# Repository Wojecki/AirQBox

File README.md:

# AirQBox
Simple air quality measuring box. 

<hr>
The project uses a custom PCB ordered from JLCPCB. It isn't required to build the box, but it makes wiring much easier and gives the whole setup a much cleaner look. The PCB is also prepared for additional components, such as a button or another I2C sensor, and does not have to be fully populated as shown in the photos above.
<hr>

<hr>
A potential use case is a home IoT weather station using web interface and OpenWeather API.
<hr>

<hr>
Bill of Materials (BOM)

| Category | Component | Description / Model | Interface |
| :--- | :--- | :--- | :--- |
| **Microcontroller** | ESP32 Dev Board | 30-pin version (15 pins per side) | — |
| **Display** | E-Ink Display Module | 4.2" 400×300 px e-Paper (Waveshare 13353) | SPI |
| **Sensor** | AHT20 + BMP280 | Temperature, humidity, and barometric pressure sensor module | I2C |
| **Sensor** | SGP30 | Indoor air quality sensor (TVOC & eCO₂) | I2C |
| **Sensor** | SCD40 | True NDIR CO₂ sensor (with temp & humidity) | I2C |
| **Sensor** | PMS5003 | Laser particulate matter sensor (PM1.0, PM2.5, PM10) | UART |

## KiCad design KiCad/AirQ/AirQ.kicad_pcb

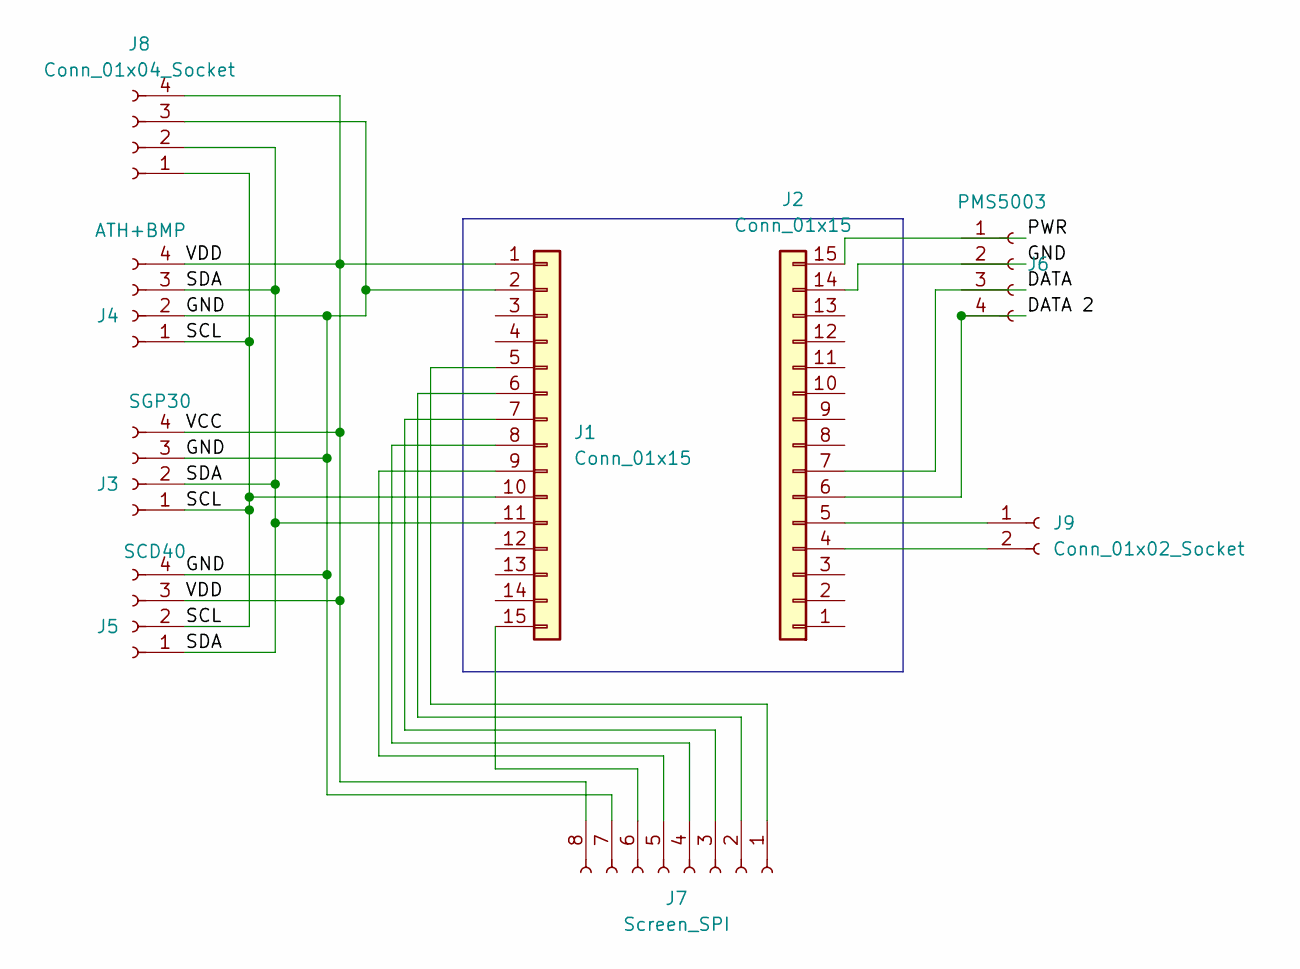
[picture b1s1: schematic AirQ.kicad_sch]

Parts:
J1, J2: Conn_01x15; PinSocket_1x15_P2.54mm_Vertical
J3: SGP30; PinSocket_1x04_P2.54mm_Vertical
J4: ATH+BMP; PinSocket_1x04_P2.54mm_Vertical
J5: SCD40; PinSocket_1x04_P2.54mm_Vertical
J6: PMS5003; PinSocket_1x04_P2.54mm_Vertical
J7: Screen_SPI; PinSocket_1x08_P2.54mm_Vertical
J8: Conn_01x04_Socket; PinSocket_1x04_P2.54mm_Vertical
J9: Conn_01x02_Socket; PinSocket_1x02_P2.54mm_Vertical

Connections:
/DATA: J2.7
/DATA 2: J2.6, J6.4 (Pin_4_4)
/GND: J1.2, J2.14, J3.3, J4.2, J5.4, J7.7, J8.3
/PWR: J2.15
/SCL: J1.10, J3.1, J4.1, J5.2, J8.1
/SDA: J1.11, J3.2, J4.3, J5.1, J8.2
/VCC: J1.1, J3.4, J4.4, J5.3, J7.8, J8.4
unnamed: J1.5, J7.1
unnamed: J1.6, J7.2
unnamed: J1.7, J7.3
unnamed: J1.8, J7.4
unnamed: J1.9, J7.5
unnamed: J1.15, J7.6
unnamed: J2.4, J9.2
unnamed: J2.5, J9.1

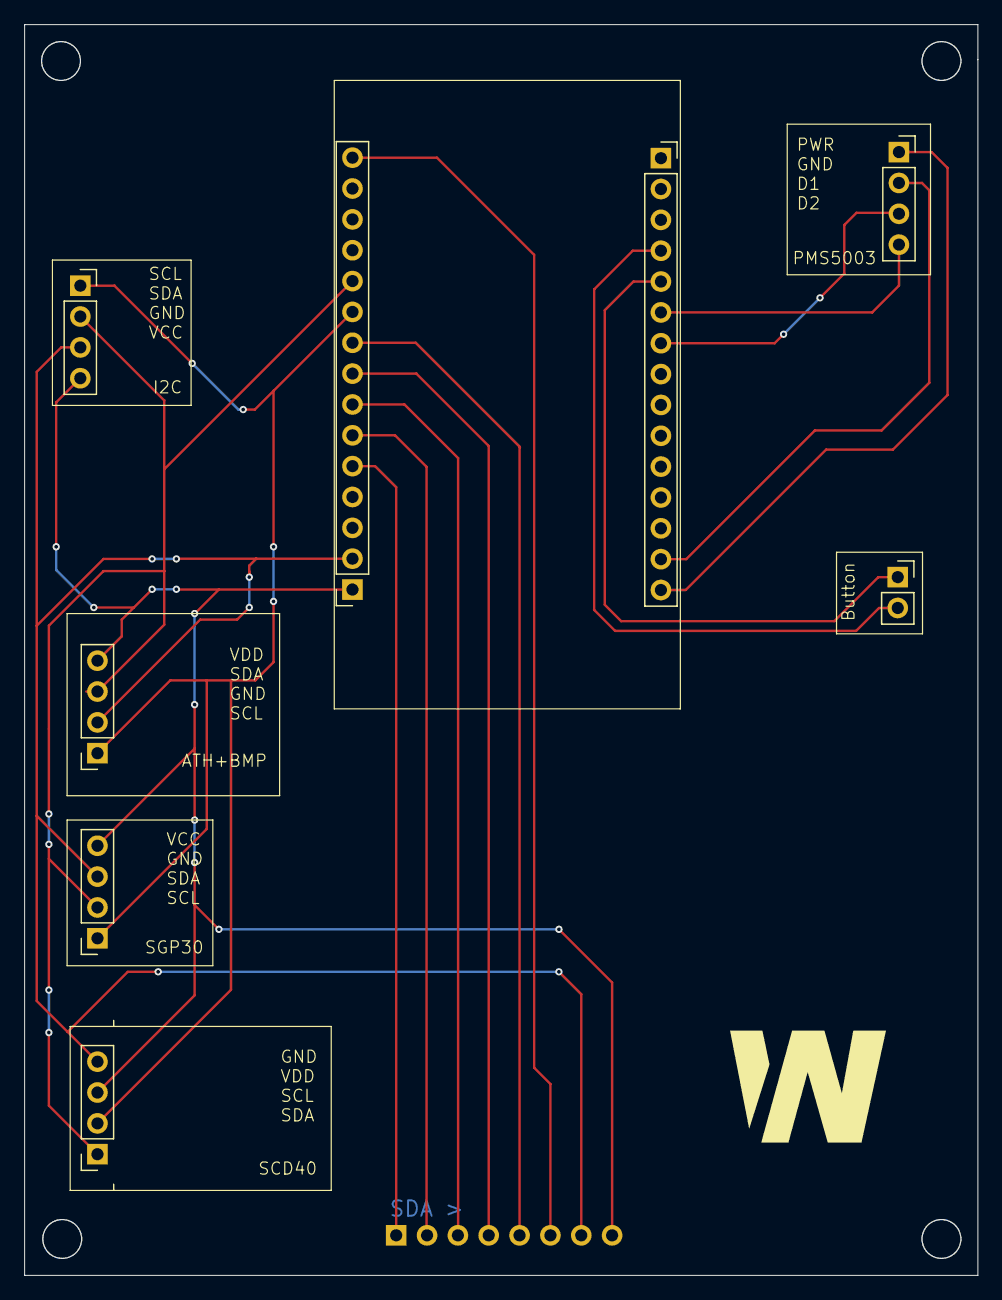
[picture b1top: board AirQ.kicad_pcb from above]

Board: 2 copper layers, 78.5 x 103.0 mm, 9 parts (1 on the bottom side), 13 nets.
